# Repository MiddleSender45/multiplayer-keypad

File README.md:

This is the design of a breakout macropad, that can be used for multiplayer games. Instead of reaching to wasd and the arrow keys this module is intended to be used, and is customizable. 

The case for the multipad is below. The bottom case has room for the USB port of the XIAO, as well as a hole to insert threaded m3 brackets. The top case is intended to be secure to the bottom via m3 screws. 

The schmematic and pcb layout are below. The central microcontroller is a XIAO ESP32 that is mounted via through-hole. The switches to be mounted are mx switches, and the keys can either be custom printed or store-bought. Two programmable LEDs are also mounted in case, and can be fit to specific requirements.

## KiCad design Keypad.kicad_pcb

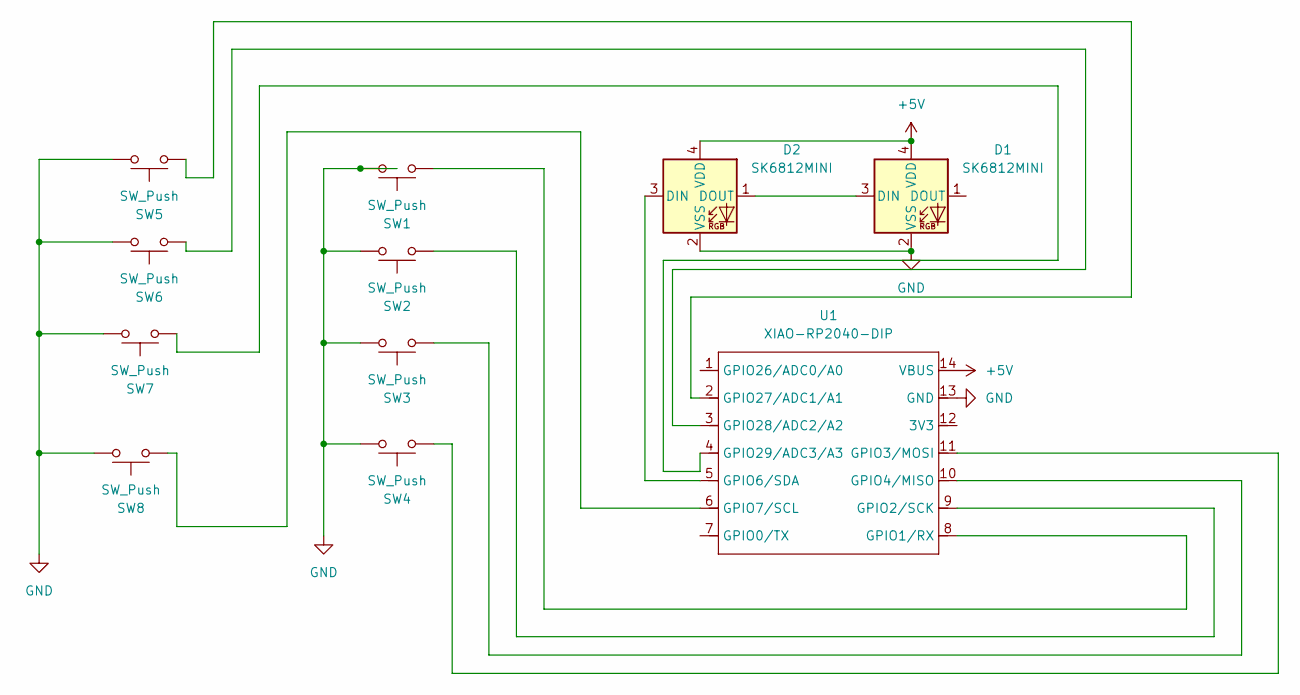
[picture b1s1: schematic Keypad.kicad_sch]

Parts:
D1, D2: SK6812MINI; LED_SK6812MINI_PLCC4_3.5x3.5mm_P1.75mm
SW1, SW2, SW3, SW4, SW5, SW6, SW7, SW8: SW_Push; SW_Cherry_MX_1.00u_PCB
U1: XIAO-RP2040-DIP

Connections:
+5V: D1.4 (VDD), D2.4 (VDD), U1.14 (VBUS)
GND: D1.2 (VSS), D2.2 (VSS), SW1.1, SW2.1, SW3.1, SW4.1, SW5.1, SW6.1, SW7.1, SW8.1, U1.13 (GND)
unnamed: D1.3 (DIN), D2.1 (DOUT)
unnamed: D2.3 (DIN), U1.5 (GPIO6/SDA)
unnamed: SW1.2, U1.8 (GPIO1/RX)
unnamed: SW2.2, U1.9 (GPIO2/SCK)
unnamed: SW4.2, U1.11 (GPIO3/MOSI)
unnamed: SW3.2, U1.10 (GPIO4/MISO)
unnamed: SW8.2, U1.6 (GPIO7/SCL)
unnamed: SW5.2, U1.2 (GPIO27/ADC1/A1)
unnamed: SW6.2, U1.3 (GPIO28/ADC2/A2)
unnamed: SW7.2, U1.4 (GPIO29/ADC3/A3)

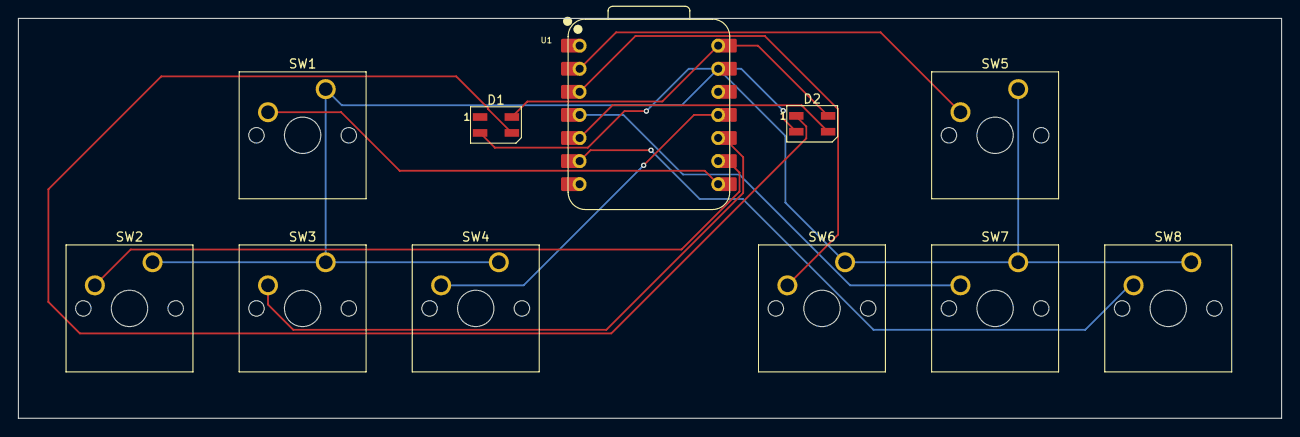
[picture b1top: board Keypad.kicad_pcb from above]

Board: 2 copper layers, 139.0 x 44.0 mm, 11 parts (0 on the bottom side), 12 nets.

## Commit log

2025-11-24 folder relocation
2025-11-25 Rename Multipad Case.stl to CAD_files/Multipad Case.stl
2025-11-25 Rename Multipad Lid.stl to CAD_files/Multipad Lid.stl
2025-11-25 Rename Multipad.step to CAD_files/Multipad.step
2025-11-25 Rename multipad_gerbers.zip to KiCad Files/multipad_gerbers.zip
2025-11-25 Rename BOM.csv to BOM/BOM.csv
2025-11-25 Rename BOM.xlsx to BOM/BOM.xlsx
2025-11-26 Rename Multipad Case (1).step to Multipad Case (1).step
2025-11-26 Rename STEP_Files/Multipad Case (1).step to CAD_Files/STEP_Files/Multipad Case (1).step
2025-11-26 Rename CAD_files/Multipad Lid (1).step to CAD_files/STEP_Files/Multipad Lid (1).step
2025-11-26 Rename CAD_files/Multipad.step to CAD_files/STEP_Files/Multipad.step
2025-11-26 Rename CAD_files/Multipad Case.stl to CAD_files/STL_Files/Multipad Case.stl
2025-11-26 Rename CAD_files/Multipad Lid.stl to CAD_files/STL_Files/Multipad Lid.stl
